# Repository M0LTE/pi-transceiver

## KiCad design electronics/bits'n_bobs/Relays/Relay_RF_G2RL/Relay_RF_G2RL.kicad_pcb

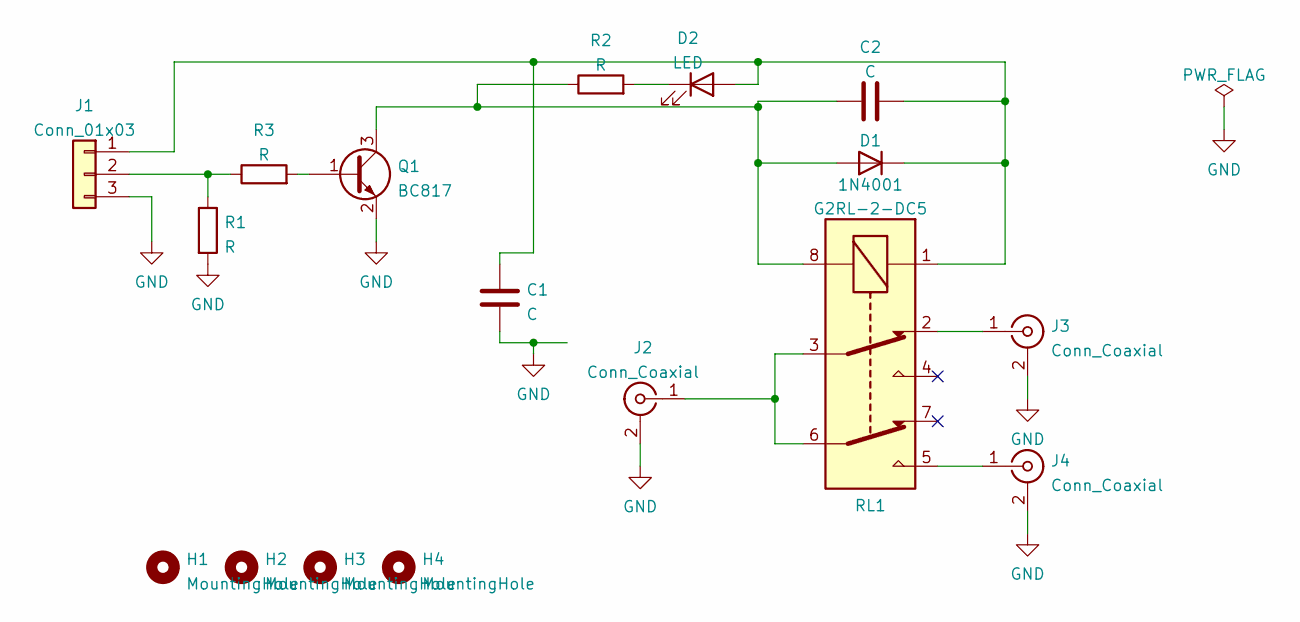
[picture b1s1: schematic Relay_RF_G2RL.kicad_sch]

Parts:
C1, C2: C; C_0603_1608Metric
D1: 1N4001; D_SOD-123
D2: LED; LED_0603_1608Metric
H1, H2, H3, H4: MountingHole; MountingHole_2.7mm_M2.5_DIN965
J1: Conn_01x03; JST_PH_B3B-PH-SM4-TB_1x03-1MP_P2.00mm_Vertical
J2, J3, J4: Conn_Coaxial; SMA_Samtec_SMA-J-P-X-ST-EM1_EdgeMount
Q1: BC817; SOT-23
R1, R2, R3: R; R_0603_1608Metric
RL1: G2RL-2-DC5; Relay_DPDT_Omron_G2RL

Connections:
GND: C1.2, J1.3, J2.2 (Ext), J3.2 (Ext), J4.2 (Ext), Q1.2 (E), R1.2
unnamed: C1.1, C2.2, D1.1 (K), D2.2 (A), J1.1, RL1.1
unnamed: C2.1, D1.2 (A), Q1.3 (C), R2.1, RL1.8
unnamed: D2.1 (K), R2.2
unnamed: J1.2, R1.1, R3.1
unnamed: J2.1 (In), RL1.3, RL1.6
unnamed: J3.1 (In), RL1.2
unnamed: J4.1 (In), RL1.5
unnamed: Q1.1 (B), R3.2

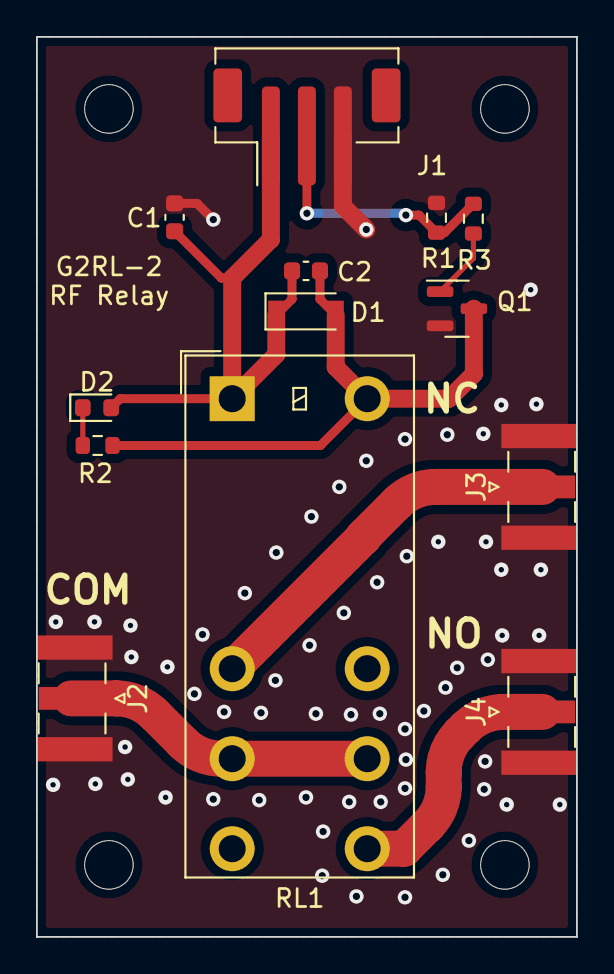
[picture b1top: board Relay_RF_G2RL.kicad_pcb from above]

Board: 2 copper layers, 30.0 x 50.0 mm, 17 parts (0 on the bottom side), 9 nets.

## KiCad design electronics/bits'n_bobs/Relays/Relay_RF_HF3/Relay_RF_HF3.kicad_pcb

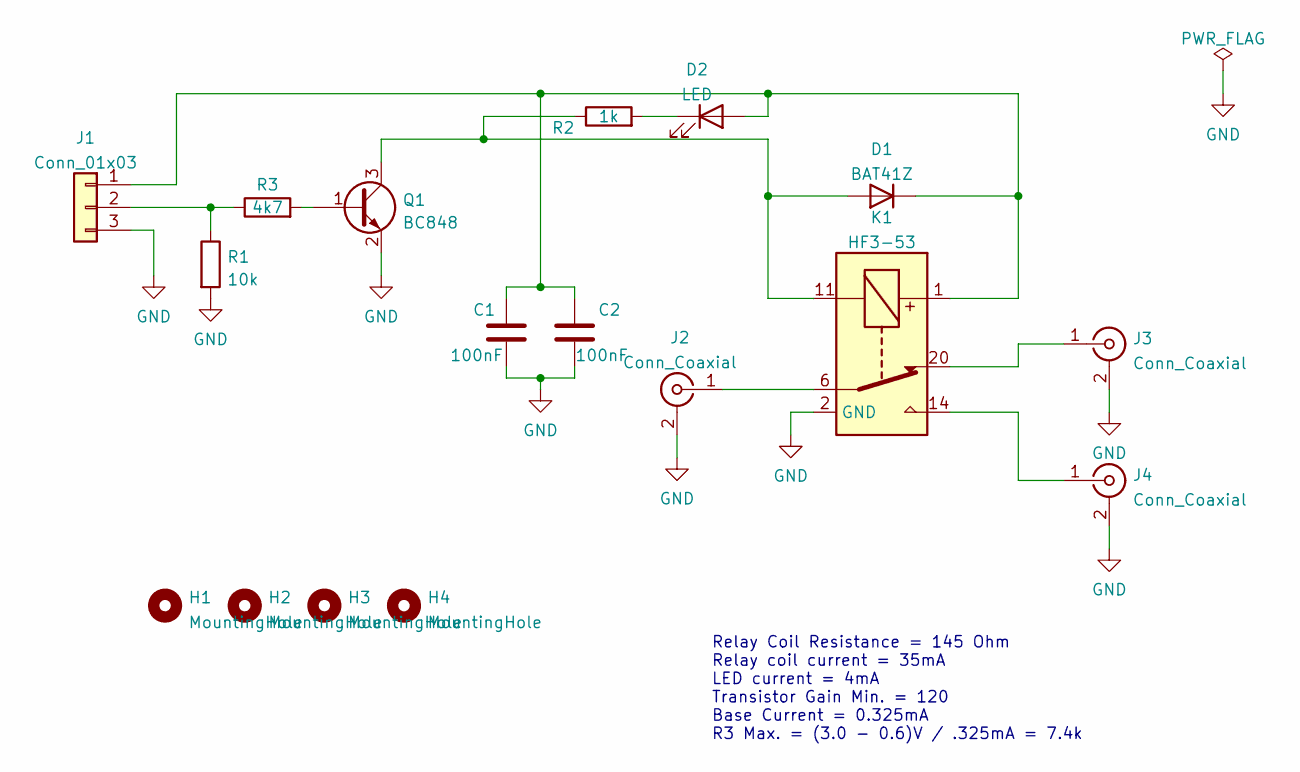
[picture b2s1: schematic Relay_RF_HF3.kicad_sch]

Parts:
C1, C2: 100nF; C_0603_1608Metric
D1: BAT41Z; D_SOD-123
D2: LED; LED_0603_1608Metric
H1, H2, H3, H4: MountingHole; MountingHole_2.7mm_M2.5_DIN965
J1: Conn_01x03; JST_PH_B3B-PH-SM4-TB_1x03-1MP_P2.00mm_Vertical
J2, J3, J4: Conn_Coaxial; SMA_Samtec_SMA-J-P-X-ST-EM1_EdgeMount
K1: HF3-53; Relay_SPDT_AXICOM_HF3Series_50ohms_Pitch1.27mm
Q1: BC848; SOT-23
R1: 10k; R_0603_1608Metric
R2: 1k; R_0603_1608Metric
R3: 4k7; R_0603_1608Metric

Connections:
GND: C1.2, C2.2, J1.3, J2.2 (Ext), J3.2 (Ext), J4.2 (Ext), K1.2 (GND), K1.5 (GND), K1.7 (GND), K1.10 (GND), K1.12 (GND), K1.13 (GND), K1.15 (GND), K1.17 (GND), K1.19 (GND), K1.21 (GND), K1.22 (GND), Q1.2 (E), R1.2
unnamed: C1.1, C2.1, D1.1 (K), D2.2 (A), J1.1, K1.1
unnamed: D1.2 (A), K1.11, Q1.3 (C), R2.1
unnamed: D2.1 (K), R2.2
unnamed: J1.2, R1.1, R3.1
unnamed: J2.1 (In), K1.6
unnamed: J3.1 (In), K1.20
unnamed: J4.1 (In), K1.14
unnamed: Q1.1 (B), R3.2

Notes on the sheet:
Relay Coil Resistance = 145 Ohm Relay coil current = 35mA LED current = 4mA Transistor Gain Min. = 120 Base Current = 0.325mA R3 Max. = (3.0 - 0.6)V / .325mA = 7.4k

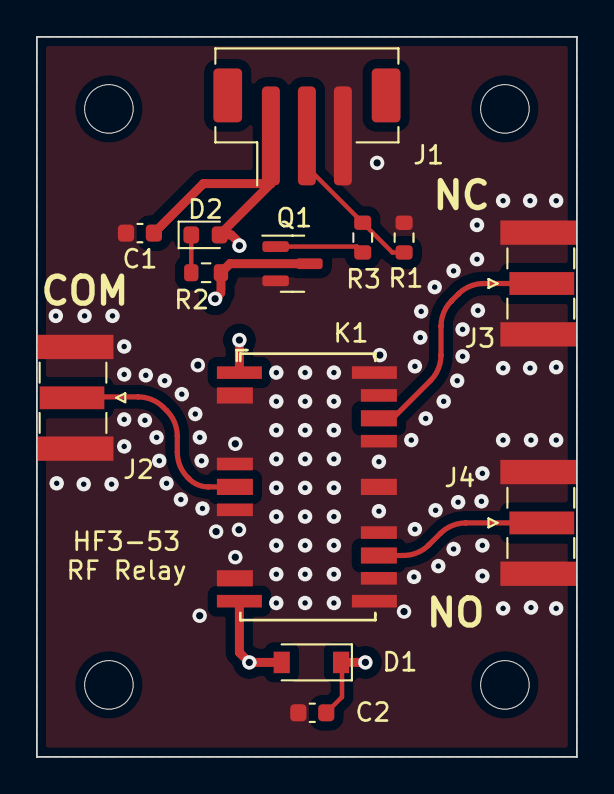
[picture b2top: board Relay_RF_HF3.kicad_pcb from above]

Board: 4 copper layers, 30.0 x 40.0 mm, 17 parts (0 on the bottom side), 9 nets.

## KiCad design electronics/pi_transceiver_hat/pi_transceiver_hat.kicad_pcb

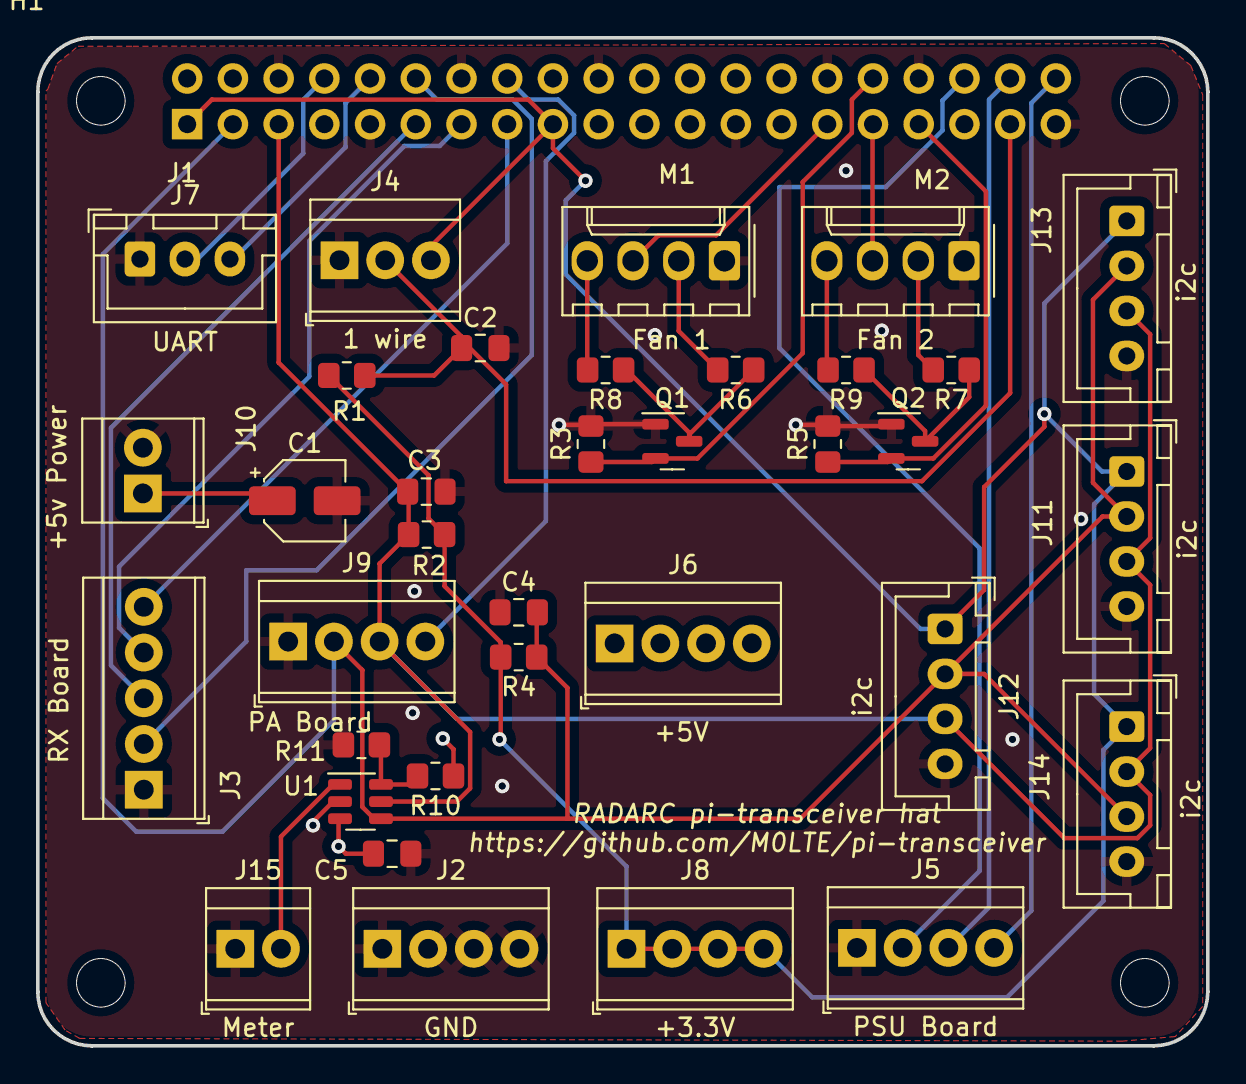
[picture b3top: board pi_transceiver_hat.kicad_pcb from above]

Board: 4 copper layers, 65.0 x 56.0 mm, 40 parts (1 on the bottom side), 26 nets.

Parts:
C1: 10uF; CP_Elec_4x5.4
C2, C3, C4, C5: 100nF; C_0805_2012Metric_Pad1.18x1.45mm_HandSolder
H1, H2, H3, H4: MountingHole_Pad; MountingHole_2.7mm_M2.5
J1: Raspberry_Pi_2_3; PinSocket_2x20_P2.54mm_Vertical
J2: GND; TerminalBlock_TE_282834-4_1x04_P2.54mm_Horizontal
J3: RX Board; TerminalBlock_TE_282834-5_1x05_P2.54mm_Horizontal
J4: 1 wire; TerminalBlock_TE_282834-3_1x03_P2.54mm_Horizontal
J5: PSU Board; TerminalBlock_TE_282834-4_1x04_P2.54mm_Horizontal
J6: +5V; TerminalBlock_TE_282834-4_1x04_P2.54mm_Horizontal
J7: UART; JST_XH_B3B-XH-A_1x03_P2.50mm_Vertical
J8: +3.3V; TerminalBlock_TE_282834-4_1x04_P2.54mm_Horizontal
J9: PA Board; TerminalBlock_TE_282834-4_1x04_P2.54mm_Horizontal
J10: +5v Power; TerminalBlock_TE_282834-2_1x02_P2.54mm_Horizontal
J11, J12, J13, J14: i2c; JST_XH_B4B-XH-A_1x04_P2.50mm_Vertical
J15: Meter; TerminalBlock_TE_282834-2_1x02_P2.54mm_Horizontal
M1: Fan 1; Molex_KK-254_AE-6410-04A_1x04_P2.54mm_Vertical
M2: Fan 2; Molex_KK-254_AE-6410-04A_1x04_P2.54mm_Vertical
Q1, Q2: 2N7000; SOT-23
R1, R2, R4, R10: 4.7K; R_0805_2012Metric_Pad1.20x1.40mm_HandSolder
R3, R5, R6, R7: 10K; R_0805_2012Metric_Pad1.20x1.40mm_HandSolder
R8, R9: 2K; R_0805_2012Metric_Pad1.20x1.40mm_HandSolder
R11: 0R; R_0805_2012Metric_Pad1.20x1.40mm_HandSolder
U1: MCP4725xxx-xCH; SOT-23-6

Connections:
+3V3: J1.1 (3V3), J1.17 (3V3), J4.3, J8.1, J8.2, J8.3, J8.4, J11.1, J12.1, J13.1, J14.1, R1.2, R2.2, R4.2
+5V: C1.1, C5.1, J1.2 (5V), J1.4 (5V), J6.1, J6.2, J6.3, J6.4, J10.1, M1.2 (+), M2.2 (+), R6.2, R7.2, R10.1, U1.3 (VDD)
GND: C1.2, C2.2, C3.1, C4.1, C5.2, J1.6 (GND), J1.9 (GND), J1.14 (GND), J1.20 (GND), J1.25 (GND), J1.30 (GND), J1.34 (GND), J1.39 (GND), J2.1, J2.2, J2.3, J2.4, J3.1, J4.1, J5.1, J7.1, J9.1, J10.2, J11.4, J12.4, J13.4, J14.4, J15.1, M1.1 (-), M2.1 (-), Q1.1 (S), Q2.1 (S), R3.2, R5.2, R11.2, U1.2 (VSS)
unnamed: C2.1, J1.37 (GPIO26), J4.2, R1.1
unnamed: C3.2, J1.5 (SCL/GPIO3), J9.3, J11.3, J12.3, J13.3, J14.2, R2.1, U1.5 (SCL)
unnamed: C4.2, J1.3 (SDA/GPIO2), J9.2, J11.2, J12.2, J13.2, J14.3, R4.1, U1.4 (SDA)
unnamed: J1.8 (GPIO14/TXD), J7.2
unnamed: J1.10 (GPIO15/RXD), J7.3
unnamed: J1.11 (GPIO17), J3.3
unnamed: J1.12 (GPIO18/PWM0), J3.2
unnamed: J1.13 (GPIO27), J3.4
unnamed: J1.15 (GPIO22), J3.5
unnamed: J1.16 (GPIO23), J9.4
unnamed: J1.29 (GCLK1/GPIO5), M1.3 (Tacho)
unnamed: J1.31 (GCLK2/GPIO6), M2.3 (Tacho)
unnamed: J1.32 (PWM0/GPIO12), Q1.2 (G), R3.1
unnamed: J1.33 (PWM1/GPIO13), Q2.2 (G), R5.1
unnamed: J1.36 (GPIO16), J5.2
unnamed: J1.38 (GPIO20/MOSI1), J5.3
unnamed: J1.40 (GPIO21/SCLK1), J5.4
unnamed: J15.2, U1.1 (VOUT)
unnamed: M1.4 (PWM), R8.2
unnamed: M2.4 (PWM), R9.2
unnamed: Q1.3 (D), R6.1, R8.1
unnamed: Q2.3 (D), R7.1, R9.1
unnamed: R10.2, R11.1, U1.6 (A0)
